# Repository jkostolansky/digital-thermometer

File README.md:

Digital Thermometer
===================

Digital Thermometer is an Arduino-based thermometer. It uses the DS18B20 1-Wire sensor.

Repository Contents
-------------------

* **/schematics**
    * **/schematics/eagle** - Eagle schematics and PCB layout
    * **/schematics/images** - Images of schematics and PCB layout
* **/digital_thermometer** - Arduino source code

The Beer-Ware License
---------------------

Juraj Kostolanský (@jkostolansky) wrote this file. As long as you retain this notice you can do whatever you want with this stuff. If we meet some day, and you think this stuff is worth it, you can buy me a beer in return.

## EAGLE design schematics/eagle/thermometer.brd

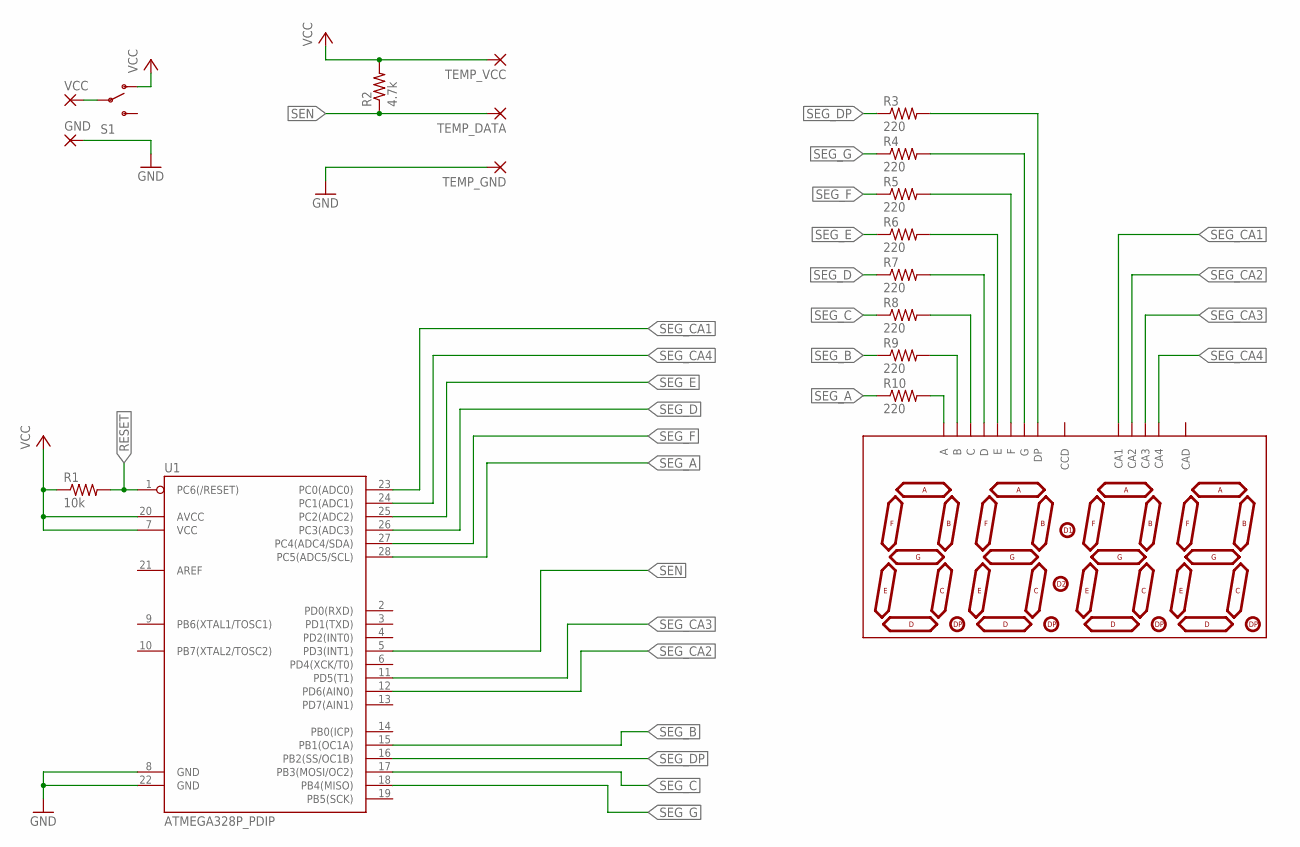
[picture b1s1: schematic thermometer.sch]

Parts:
GND: 2,54/0,8
R1: 10k; R0805
R2: 4.7k; R0805
R3, R4, R5, R6, R7, R8, R9, R10: 220; R0805
S1: SWITCH-SPDTPTH; SWITCH-SPDT
TEMP_DATA: 2,54/0,8
TEMP_GND: 2,54/0,8
TEMP_VCC: 2,54/0,8
U1: ATMEGA328P_PDIP; DIL28-3
U2: 5461BSDIP14; 5461BS
VCC: 2,54/0,8

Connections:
GND: GND.1, TEMP_GND.1, U1.8 (GND), U1.22 (GND)
unnamed: R10.2, U2.A
unnamed: R9.2, U2.B
unnamed: R7.2, U2.D
unnamed: R8.2, U2.C
unnamed: R6.2, U2.E
unnamed: R5.2, U2.F
unnamed: R4.2, U2.G
unnamed: R3.2, U2.DP
unnamed: S1.2, VCC.1
RESET: R1.2, U1.1 (PC6(/RESET))
SEG_A: R10.1, U1.28 (PC5(ADC5/SCL))
SEG_B: R9.1, U1.15 (PB1(OC1A))
SEG_C: R8.1, U1.17 (PB3(MOSI/OC2))
SEG_CA1: U1.23 (PC0(ADC0)), U2.CA1
SEG_CA2: U1.12 (PD6(AIN0)), U2.CA2
SEG_CA3: U1.11 (PD5(T1)), U2.CA3
SEG_CA4: U1.24 (PC1(ADC1)), U2.CA4
SEG_D: R7.1, U1.26 (PC3(ADC3))
SEG_DP: R3.1, U1.16 (PB2(SS/OC1B))
SEG_E: R6.1, U1.25 (PC2(ADC2))
SEG_F: R5.1, U1.27 (PC4(ADC4/SDA))
SEG_G: R4.1, U1.18 (PB4(MISO))
SEN: R2.1, TEMP_DATA.1, U1.5 (PD3(INT1))
VCC: R1.1, R2.2, S1.1 (O), TEMP_VCC.1, U1.7 (VCC), U1.20 (AVCC)

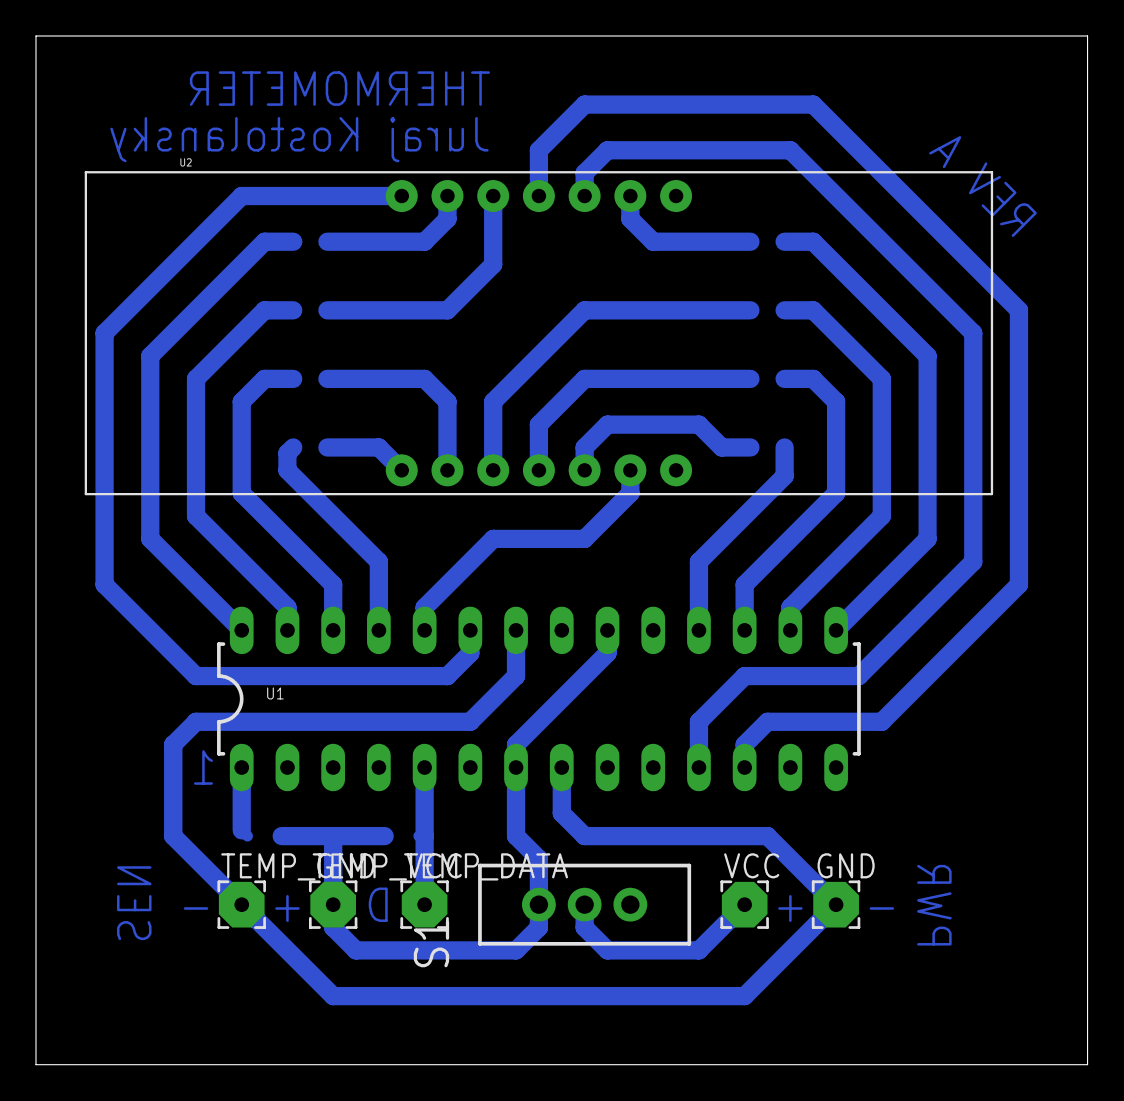
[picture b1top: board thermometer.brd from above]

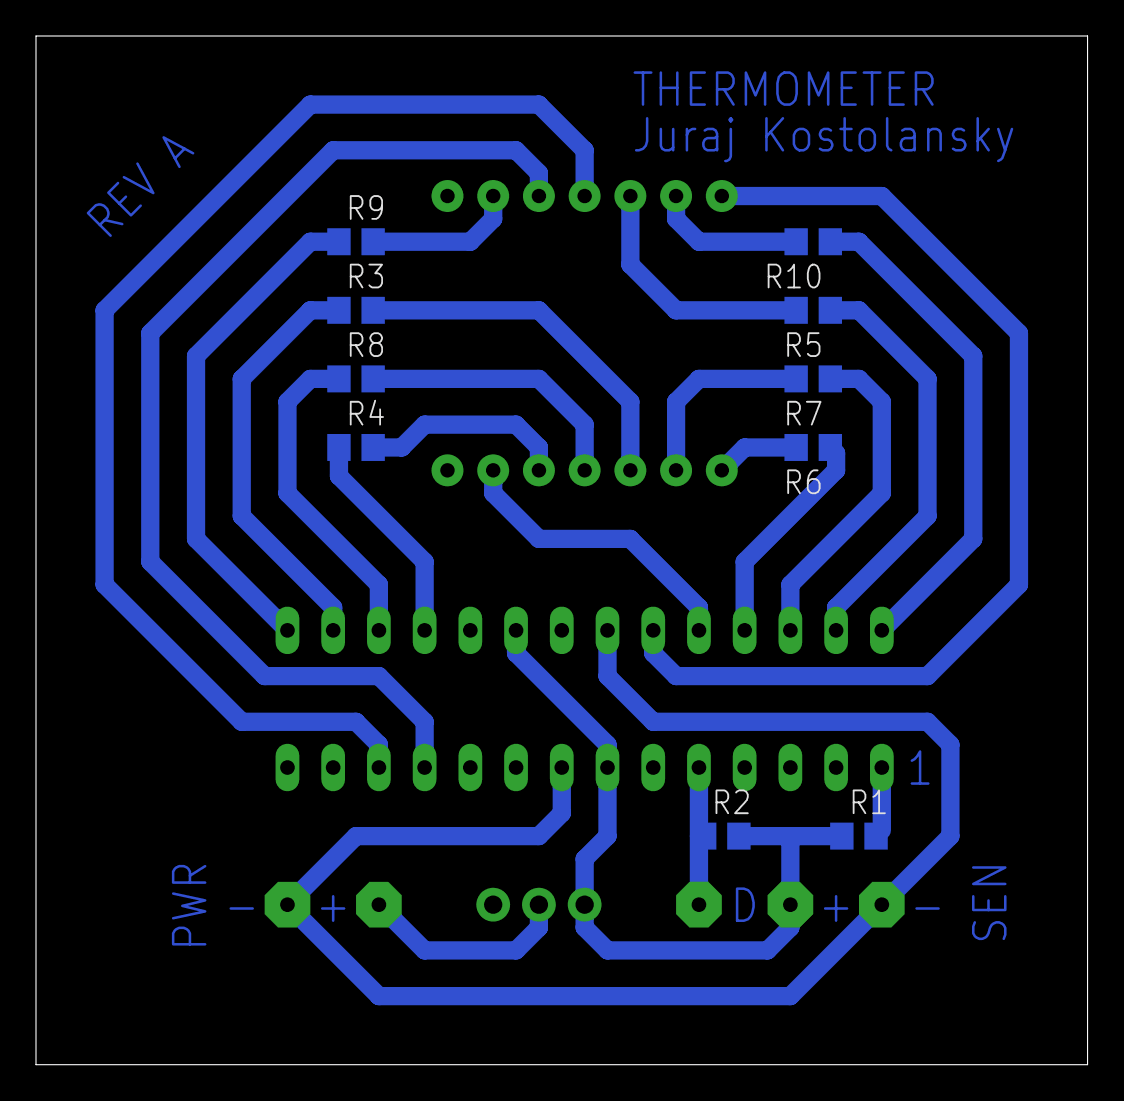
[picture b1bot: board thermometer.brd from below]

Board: 2 copper layers, 58.4 x 57.1 mm, 18 parts (10 on the bottom side), 25 nets.

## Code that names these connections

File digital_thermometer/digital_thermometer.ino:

/*
  Digital Thermometer
  
  Reads temperature from a Dallas temperature sensor DS18B20
  and displays it on a 4-digit 7-segment display 5461BS
 
  by Juraj Kostolansky

 */

#include <OneWire.h>
#include <DallasTemperature.h>
#include <SevSeg.h>

// pinout
#define ONE_WIRE_BUS   3
#define SEG_A         19
#define SEG_B          9
#define SEG_C         11
#define SEG_D         17
#define SEG_E         16
#define SEG_F         18
#define SEG_G         12
#define SEG_DP        10
#define SEG_CA1       14
#define SEG_CA2        6
#define SEG_CA3        5
#define SEG_CA4       15

// settings
#define SEG_TYPE COMMON_ANODE
#define SEG_DIGITS 4
// resolution: 9 -> .5°C, 10 -> .25°C, 11 -> .125°C, 12 -> .0625°C
#define SIG_RESOLUTION 12
#define SEG_BRIGHTNESS 100

// One Wire and Dallas sensor setup
OneWire oneWire(ONE_WIRE_BUS); 
DallasTemperature sensors(&oneWire);
DeviceAddress tempDeviceAddress;

// SevSeg library setup
SevSeg screen;

// global variables
unsigned int temp_delay;
float temp;
int tempDigits;
unsigned long tempRequestEndTime;
char screenString[10];

void setup() {
  // start up the display
  screen.Begin(SEG_TYPE, SEG_DIGITS,
               SEG_CA1, SEG_CA2, SEG_CA3, SEG_CA4,
               SEG_A, SEG_B, SEG_C, SEG_D, SEG_E, SEG_F, SEG_G, SEG_DP);
  screen.SetBrightness(SEG_BRIGHTNESS);
  
  // start up the sensor
  sensors.begin();
  sensors.getAddress(tempDeviceAddress, 0);
  sensors.setWaitForConversion(false);
  sensors.setResolution(SIG_RESOLUTION);
  
  // request first temperature
  sensors.requestTemperatures();
  tempRequestEndTime = millis() + sensors.millisToWaitForConversion(SIG_RESOLUTION);
  // and wait for first temp to prevent false startup reading
  delay(sensors.millisToWaitForConversion(SIG_RESOLUTION));  
}

void loop() {
  // get temperature
  if(tempRequestEndTime < millis()) {
    temp = sensors.getTempC(tempDeviceAddress);
    sensors.requestTemperatures();
    tempRequestEndTime = millis() + sensors.millisToWaitForConversion(SIG_RESOLUTION);
  }  
  // round temp and convert to int (digits only)
  tempDigits = round(temp * 10.0);  
  // convert temperature to string
  if(temp >= 0) {
    sprintf(screenString, "%4d", tempDigits); 
  } else {
    // workaround for "-.5 or leading zeros" problem
    screenString[0] = '-';
    sprintf(&screenString[1], "%3d", tempDigits * -1);
  }  
  // and display it (one decimal place)
  screen.DisplayString(screenString, 4);
}

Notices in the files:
parts and their libraries:
SparkFun-DigitalIC: Licensing: Creative Commons ShareAlike 4.0 International - https://creativecommons.org/licenses/by-sa/4.0
